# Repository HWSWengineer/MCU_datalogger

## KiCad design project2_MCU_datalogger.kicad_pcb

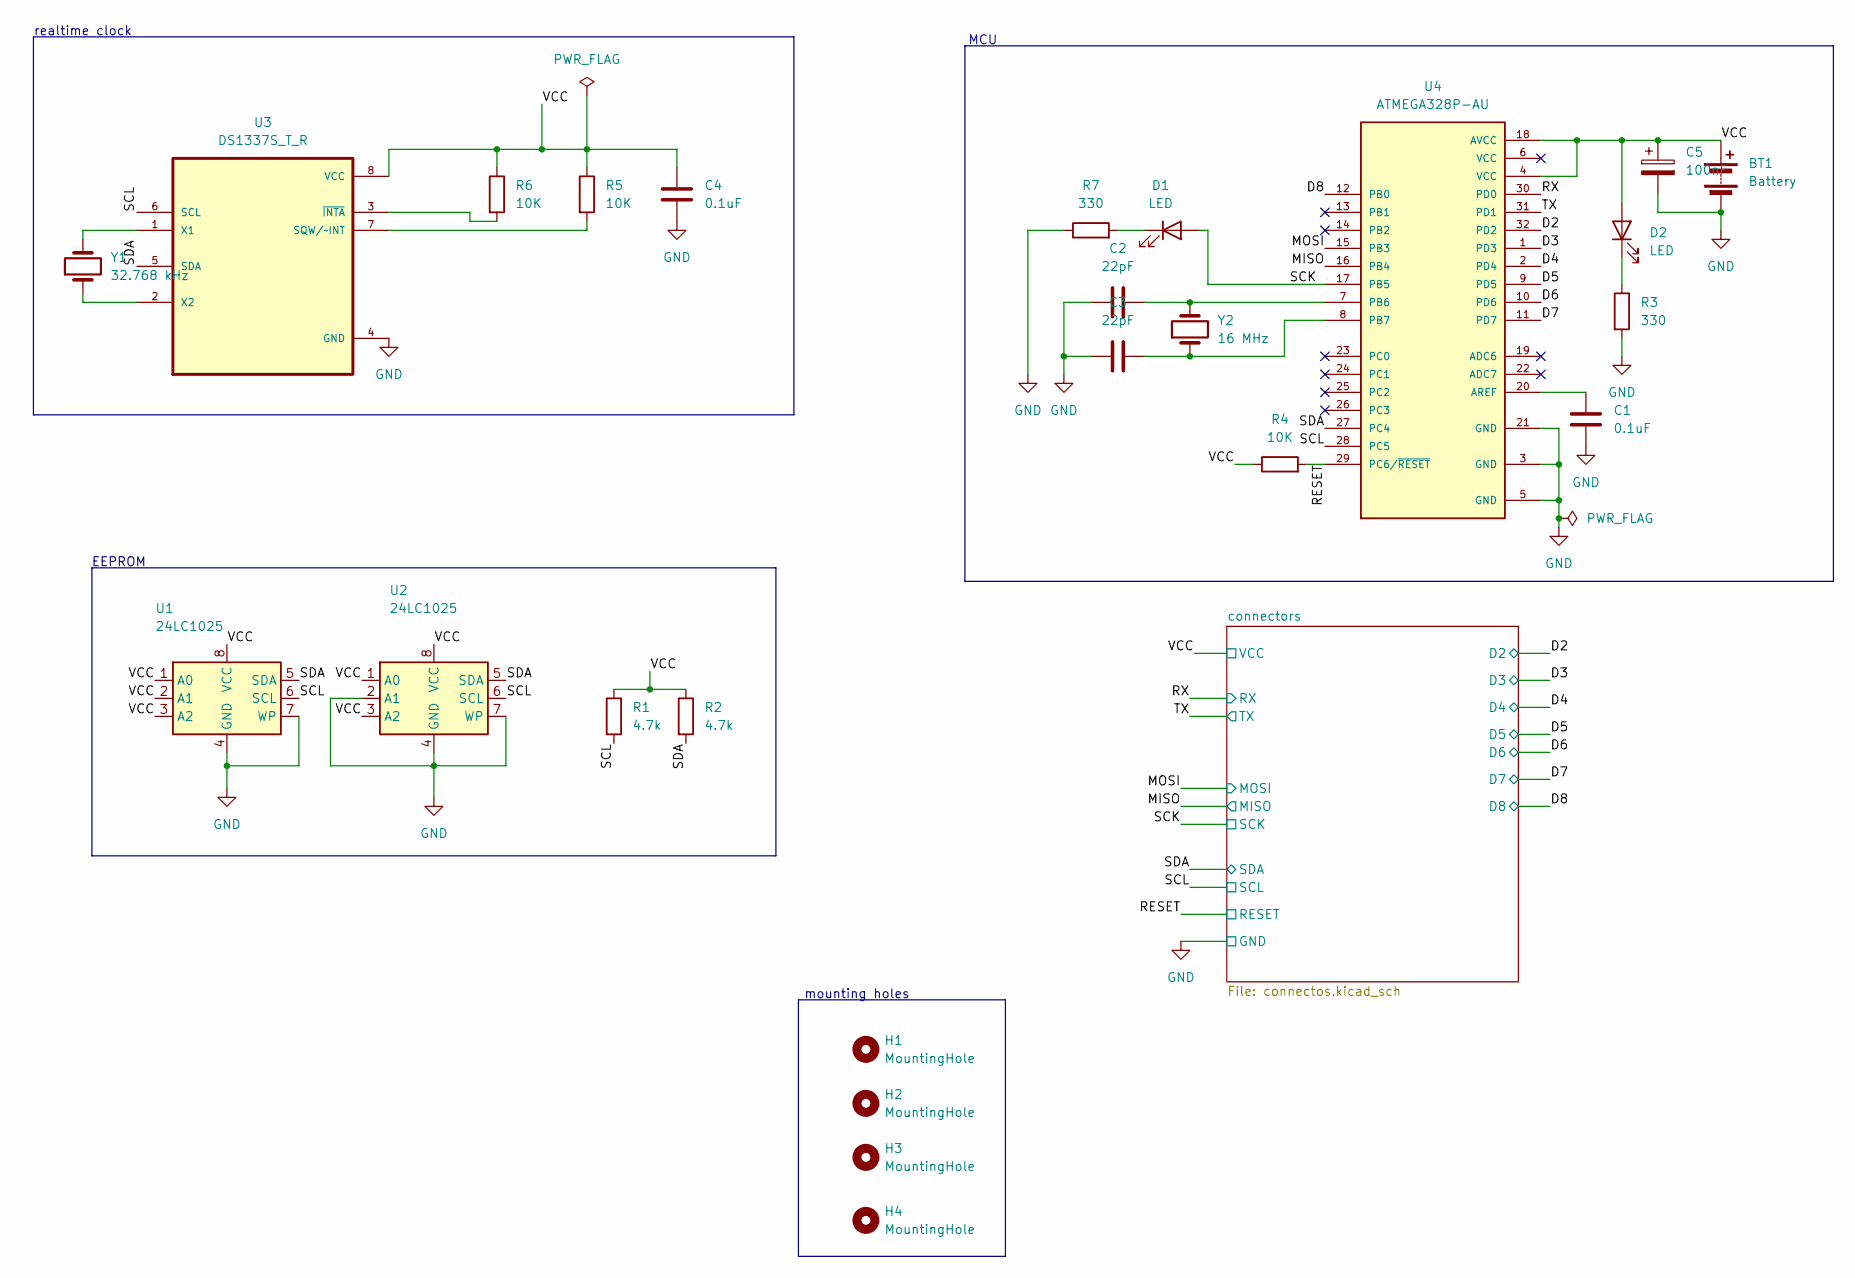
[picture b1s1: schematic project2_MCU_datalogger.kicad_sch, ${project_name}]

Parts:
BT1: Battery; PinHeader_1x02_P2.54mm_Vertical
C1, C4: 0.1uF; C_0805_2012Metric
C2, C3: 22pF; C_0805_2012Metric
C5: 100nF; C_0805_2012Metric
D1, D2: LED; LED_0805_2012Metric
H1, H2, H3, H4: MountingHole; MountingHole_2.1mm
R1, R2: 4.7k; R_0805_2012Metric
R3, R7: 330; R_0805_2012Metric
R4, R5, R6: 10K; R_0805_2012Metric
U1, U2: 24LC1025; SOIC-8_5.23x5.23mm_P1.27mm
U3: DS1337S_T_R; SOIC127P600X175-8N
U4: ATMEGA328P-AU; QFP80P900X900X120-32N; PARTREV 8271A
Y1: 32.768 kHz; Crystal_SMD_5032-2Pin_5.0x3.2mm_HandSoldering
Y2: 16 MHz; Crystal_SMD_5032-2Pin_5.0x3.2mm_HandSoldering

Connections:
/D2: U4.32 (PD2); also elsewhere on the board
/D3: U4.1 (PD3); also elsewhere on the board
/D4: U4.2 (PD4); also elsewhere on the board
/D5: U4.9 (PD5); also elsewhere on the board
/D6: U4.10 (PD6); also elsewhere on the board
/D7: U4.11 (PD7); also elsewhere on the board
/D8: U4.12 (PB0); also elsewhere on the board
/MISO: U4.16 (PB4); also elsewhere on the board
/MOSI: U4.15 (PB3); also elsewhere on the board
/RESET: R4.2, U4.29 (PC6/~RESET); also elsewhere on the board
/RX: U4.30 (PD0); also elsewhere on the board
/SCK: D1.2 (A), R1.2, U1.6 (SCL), U2.6 (SCL), U3.6 (SCL), U4.17 (PB5), U4.28 (PC5); also elsewhere on the board
/SDA: R2.2, U1.5 (SDA), U2.5 (SDA), U3.5 (SDA), U4.27 (PC4); also elsewhere on the board
/TX: U4.31 (PD1); also elsewhere on the board
/VCC: BT1.1 (+), C4.1, C5.1, D2.2 (A), R1.1, R2.1, R4.1, R5.1, R6.1, U1.1 (A0), U1.2 (A1), U1.3 (A2), U1.8 (VCC), U2.1 (A0), U2.3 (A2), U2.8 (VCC), U3.8 (VCC), U4.4 (VCC), U4.18 (AVCC); also elsewhere on the board
GND: BT1.2 (-), C1.1, C2.1, C3.1, C4.2, C5.2, R3.2, R7.1, U1.4 (GND), U1.7 (WP), U2.2 (A1), U2.4 (GND), U2.7 (WP), U3.4 (GND), U4.3 (GND), U4.5 (GND), U4.21 (GND); also elsewhere on the board
unnamed: D1.1 (K), R7.2
unnamed: D2.1 (K), R3.1
unnamed: R5.2, U3.7 (SQW/~INT)
unnamed: U3.1 (X1), Y1.2
unnamed: U3.2 (X2), Y1.1
unnamed: R6.2, U3.3 (~INTA)
unnamed: C1.2, U4.20 (AREF)
unnamed: C2.2, U4.7 (PB6), Y2.2
unnamed: C3.2, U4.8 (PB7), Y2.1

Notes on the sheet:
MCU
realtime clock
mounting holes
EEPROM

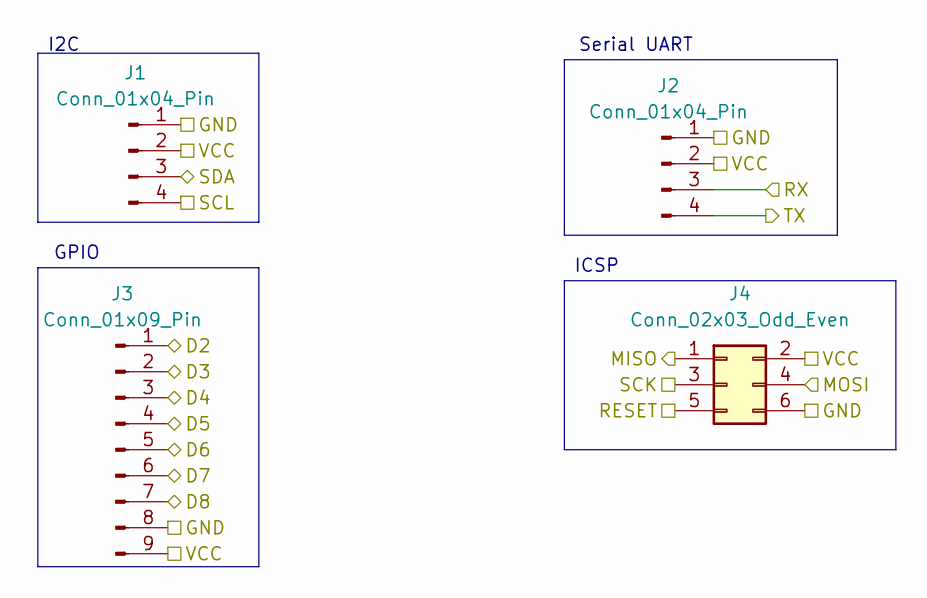
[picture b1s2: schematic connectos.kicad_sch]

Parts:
J1, J2: Conn_01x04_Pin; PinHeader_1x04_P2.54mm_Vertical
J3: Conn_01x09_Pin; PinHeader_1x09_P2.54mm_Vertical
J4: Conn_02x03_Odd_Even; PinHeader_2x03_P2.54mm_Vertical

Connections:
/D2: J3.1; also elsewhere on the board
/D3: J3.2; also elsewhere on the board
/D4: J3.3; also elsewhere on the board
/D5: J3.4; also elsewhere on the board
/D6: J3.5; also elsewhere on the board
/D7: J3.6; also elsewhere on the board
/D8: J3.7; also elsewhere on the board
/MISO: J4.1; also elsewhere on the board
/MOSI: J4.4; also elsewhere on the board
/RESET: J4.5; also elsewhere on the board
/RX: J2.3; also elsewhere on the board
/SCK: J1.4, J4.3; also elsewhere on the board
/SDA: J1.3; also elsewhere on the board
/TX: J2.4; also elsewhere on the board
/VCC: J1.2, J2.2, J3.9, J4.2; also elsewhere on the board
GND: J1.1, J2.1, J3.8, J4.6; also elsewhere on the board

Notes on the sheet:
ICSP
Serial UART
GPIO
I2C

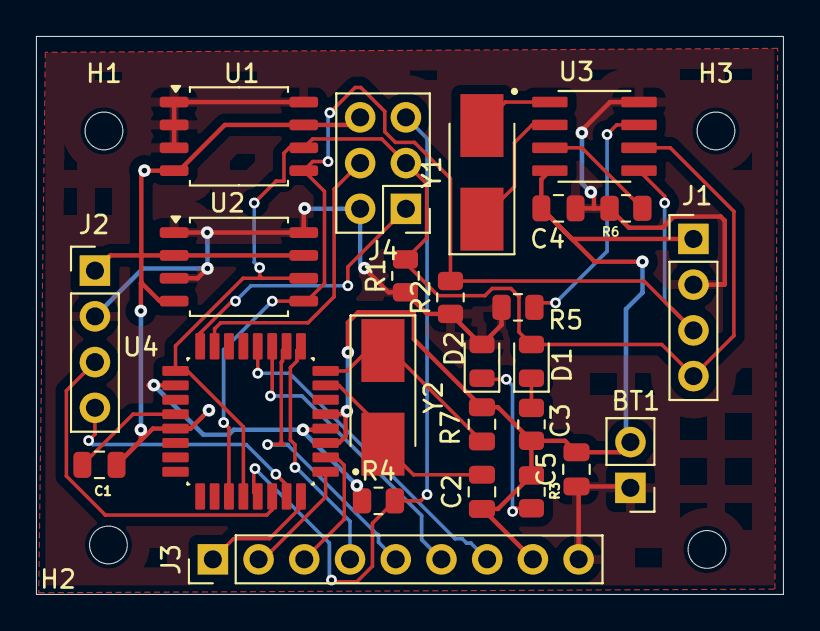
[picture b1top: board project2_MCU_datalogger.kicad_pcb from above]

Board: 2 copper layers, 41.5 x 31.0 mm, 29 parts (0 on the bottom side), 25 nets.

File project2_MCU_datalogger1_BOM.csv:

Reference,Value,Datasheet,Footprint,Qty,DNP
BT1,Battery,~,Connector_PinHeader_2.54mm:PinHeader_1x02_P2.54mm_Vertical,1,
"C1,C4",0.1uF,~,Capacitor_SMD:C_0805_2012Metric,2,
"C2,C3",22pF,~,Capacitor_SMD:C_0805_2012Metric,2,
C5,100nF,~,Capacitor_SMD:C_0805_2012Metric,1,
"D1,D2",LED,~,LED_SMD:LED_0805_2012Metric,2,
"J1,J2",Conn_01x04_Pin,~,Connector_PinHeader_2.54mm:PinHeader_1x04_P2.54mm_Vertical,2,
J3,Conn_01x09_Pin,~,Connector_PinHeader_2.54mm:PinHeader_1x09_P2.54mm_Vertical,1,
J4,Conn_02x03_Odd_Even,~,Connector_PinHeader_2.54mm:PinHeader_2x03_P2.54mm_Vertical,1,
"R1,R2",4.7k,~,Resistor_SMD:R_0805_2012Metric,2,
"R3,R7",330,~,Resistor_SMD:R_0805_2012Metric,2,
"R4,R5,R6",10K,~,Resistor_SMD:R_0805_2012Metric,3,
"U1,U2",24LC1025,http://ww1.microchip.com/downloads/en/DeviceDoc/21941B.pdf,Package_SO:SOIC-8_5.23x5.23mm_P1.27mm,2,
U3,DS1337S_T_R,,DS1337S_T_R:SOIC127P600X175-8N,1,
U4,ATMEGA328P-AU,,ATMEGA328P-AU:QFP80P900X900X120-32N,1,
Y1,32.768 kHz,~,Crystal:Crystal_SMD_5032-2Pin_5.0x3.2mm_HandSoldering,1,
Y2,16 MHz,~,Crystal:Crystal_SMD_5032-2Pin_5.0x3.2mm_HandSoldering,1,
